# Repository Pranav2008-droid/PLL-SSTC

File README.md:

# PLL SSTC

## Overview
The PLL SSTC stands for Phase Locked Loop Solid State Tesla coil. This device produces high voltage sparks that resemble lightning by exciting a secondary coil at its resonant frequency.

This system tracks the resonant frequency using a Phase Locked Loop (PLL) IC: CD4046. It uses the output from the PLL to drive a full bridge switching circuit at around 300-325VDC.

It also has the capability to play audio through both Amplitude Modulation (AM) and Frequency Modulation (FM). It operates at 250kHz and should switch power in the Kilowatt range.

> ⚠️ High Voltage Warning  
> This project involves potentially lethal voltages and high-frequency/high-power switching. Do not build or operate it unless you understand the relevant electrical safety risks.

## Gate Driver
I'm using a TC4428 paired with 2 N-channel/P-channel dual MOSFET ICs to produce an amplified signal capable of producing higher driving currents. Any MOSFET driving IC with one inverting and one non-inverting output should work in the PCB, such as the UCC27425.

## GDT
The Gate Drive Transformer must be large enough to not saturate from driving currents and be of the correct material to work properly under such high frequencies.

## Mosfets
My circuit shows IRFP460s as the full bridge switches, but they are a bit outdated and inefficient. Much better alternatives exist — IGBTs can also be used instead.

## Primary
Make sure the primary impedance is high enough such that your switches can handle the currents.

## Demo
Demo of the amplitude modification music played through an attiny interupter: https://www.youtube.com/shorts/cHrE9xm2R9Q

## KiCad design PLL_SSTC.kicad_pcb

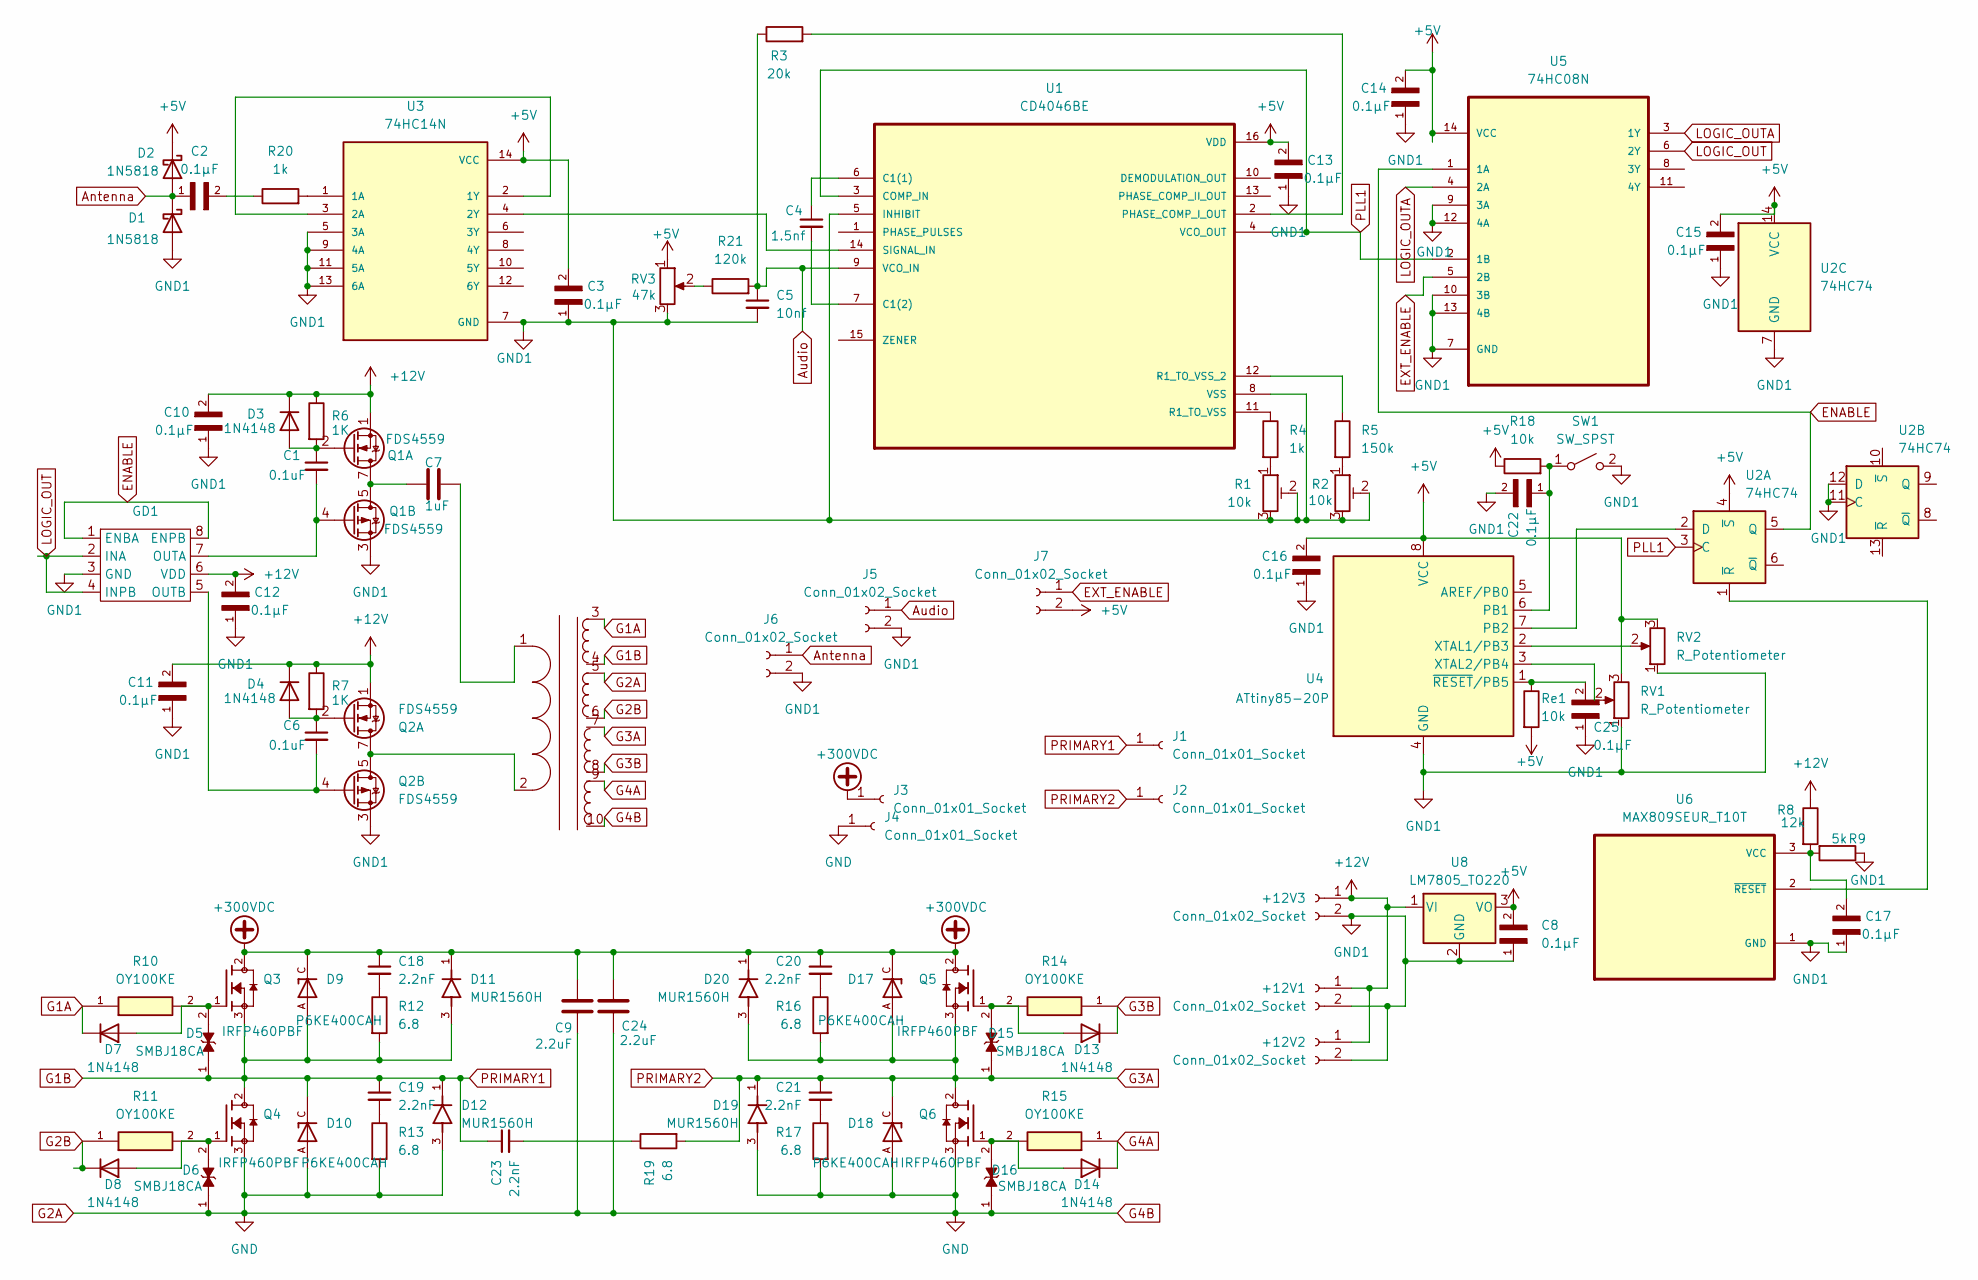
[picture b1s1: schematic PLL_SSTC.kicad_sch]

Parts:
+12V1, +12V2, +12V3: Conn_01x02_Socket; PinHeader_1x02_P2.54mm_Vertical
C1, C6: 0.1uF; C_0603_1608Metric_Pad1.08x0.95mm_HandSolder
C2, C3, C8, C10, C11, C12, C13, C14, C15, C16, C17, C22, C25: 0.1µF; C_0603_1608Metric_Pad1.08x0.95mm_HandSolder; PARTREV 081816
C4: 1.5nf; C_Rect_L7.0mm_W2.5mm_P5.00mm
C5: 10nf; C_Rect_L7.0mm_W2.5mm_P5.00mm
C7: 1uF; C_Rect_L31.5mm_W15.0mm_P27.50mm_MKS4
C9, C24: 2.2uF; C_Rect_L31.5mm_W15.0mm_P27.50mm_MKS4
C18, C19, C20, C21, C23: 2.2nF; C_Rect_L7.0mm_W2.5mm_P5.00mm
D1, D2: 1N5818; D_DO-41_SOD81_P10.16mm_Horizontal
D3, D4, D7, D8, D13, D14: 1N4148; D_DO-35_SOD27_P7.62mm_Horizontal
D5, D6, D15, D16: SMBJ18CA; DIOM4336X265N; PARTREV I2102
D9, D10, D17, D18: P6KE400CAH; DIOAD1300W80L670D310; PARTREV K2105
D11, D12, D19, D20: MUR1560H; TO508P997X444X1905-2; PARTREV F
GD1: DIP-8_W7.62mm_LongPads
J1, J2, J3, J4: Conn_01x01_Socket; SolderWire-4sqmm_1x01_D3mm_OD6mm
J5, J6, J7: Conn_01x02_Socket; TerminalBlock_Phoenix_MKDS-3-2-5.08_1x02_P5.08mm_Horizontal
Q1, Q2: FDS4559; SOIC-8_3.9x4.9mm_P1.27mm
Q3, Q4, Q5, Q6: IRFP460PBF; TO546P1587X531X2511-3; PARTREV A
R1, R2: 10k; TRIM_3296W-1-250
R3: 20k; R_Axial_DIN0207_L6.3mm_D2.5mm_P10.16mm_Horizontal
R4, R20: 1k; R_Axial_DIN0207_L6.3mm_D2.5mm_P10.16mm_Horizontal
R5: 150k; R_Axial_DIN0207_L6.3mm_D2.5mm_P10.16mm_Horizontal
R6, R7: 1K; R_Axial_DIN0207_L6.3mm_D2.5mm_P10.16mm_Horizontal
R8: 12k; R_Axial_DIN0207_L6.3mm_D2.5mm_P10.16mm_Horizontal
R9: 5k; R_Axial_DIN0207_L6.3mm_D2.5mm_P10.16mm_Horizontal
R10, R11, R14, R15: OY100KE; R_Axial_DIN0414_L11.9mm_D4.5mm_P7.62mm_Vertical; MOUSER_PART_NUMBER 588-OY-10-E
R12, R13, R16, R17, R19: 6.8; R_Axial_DIN0922_L20.0mm_D9.0mm_P7.62mm_Vertical
R18: 10k; R_Axial_DIN0207_L6.3mm_D2.5mm_P10.16mm_Horizontal
R21: 120k; R_Axial_DIN0207_L6.3mm_D2.5mm_P10.16mm_Horizontal
RV1, RV2: R_Potentiometer; Potentiometer_Bourns_3296X_Horizontal
RV3: 47k; Potentiometer_Bourns_3296X_Horizontal
Re1: 10k; R_Axial_DIN0204_L3.6mm_D1.6mm_P1.90mm_Vertical
SW1: SW_SPST; TerminalBlock_4Ucon_1x02_P3.50mm_Horizontal
U1: CD4046BE; DIP794W45P254L1969H508Q16
U2: 74HC74; CERDIP-14_W7.62mm_SideBrazed_LongPads_Socket
U3: 74HC14N; DIP764W47P254L1920H431Q14
U4: ATtiny85-20P; DIP-8_W7.62mm
U5: 74HC08N; DIP254P762X420-14; MPN 74HC08N
U6: MAX809SEUR_T10T; SOT95P237X112-3N
U7: GDT_1P4S
U8: LM7805_TO220; TO-220-3_Vertical

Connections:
+5V: C3.2, C8.2, C13.2, C14.2, C15.2, C16.2, D2.1 (K), J7.2, R18.1, RV1.3, RV2.3, RV3.1, Re1.2, U1.16 (VDD), U2.4 (~S), U2.14 (VCC), U3.14 (VCC), U4.8 (VCC), U5.14 (VCC), U8.3 (VO)
+12V: +12V1.1, +12V2.1, +12V3.1, C10.2, C11.2, C12.2, D3.1 (K), D4.1 (K), GD1.6 (VDD), Q1.1 (S1), Q2.1 (S1), R6.1, R7.1, R8.1, U8.1 (VI)
+300VDC: C9.1, C18.1, C20.1, C24.1, D9.C, D11.1, D17.C, D20.1, J3.1 (Pin_1_1), Q3.2, Q5.2
Antenna: C2.1, D1.1 (K), D2.2 (A), J6.1
Audio: C5.1, J5.1, R3.1, R21.2, U1.9 (VCO_IN)
ENABLE: GD1.1 (ENBA), GD1.8 (ENPB), U2.5 (Q), U5.1 (1A)
EXT_ENABLE: J7.1, U5.5 (2B)
G1A: D7.1 (K), R10.1, U7.3 (1A)
G1B: C19.1, C23.1, D5.1, D9.A, D10.C, D11.3, D12.1, J1.1 (Pin_1_1), Q3.3, Q4.2, R12.2, U7.4 (1B)
G2A: C9.2, C24.2, D6.1, D10.A, D12.3, D16.1, D18.A, D19.3, J4.1 (Pin_1_1), Q4.3, Q6.3, R13.2, R17.2, U7.5 (2A), U7.10 (4B)
G2B: D8.1 (K), R11.1, U7.6 (2B)
G3A: C21.1, D15.1, D17.A, D18.C, D19.1, D20.3, J2.1 (Pin_1_1), Q5.3, Q6.2, R16.2, R19.2, U7.7 (3A)
G3B: D13.1 (K), R14.1, U7.8 (3B)
G4A: D14.1 (K), R15.1, U7.9 (4A)
GND1: +12V1.2, +12V2.2, +12V3.2, C3.1, C5.2, C8.1, C10.1, C11.1, C12.1, C13.1, C14.1, C15.1, C16.1, C17.1, C22.2, C25.1, D1.2 (A), GD1.3 (GND), J5.2, J6.2, Q1.3 (S2), Q2.3 (S2), R1.2, R1.3, R2.2, R2.3, R9.1, RV1.1, RV2.1, RV3.3, SW1.2 (B), U1.5 (INHIBIT), U1.8 (VSS), U2.7 (GND), U2.11 (C), U2.12 (D), U3.5 (3A), U3.7 (GND), U3.9 (4A), U3.11 (5A), U3.13 (6A), U4.4 (GND), U5.7 (GND), U5.9 (3A), U5.10 (3B), U5.12 (4A), U5.13 (4B), U6.1 (GND), U8.2 (GND)
LOGIC_OUT: GD1.2 (INA), GD1.4 (INPB), U5.6 (2Y)
LOGIC_OUTA: U5.3 (1Y), U5.4 (2A)
unnamed: C2.2, R20.1
unnamed: C7.1, Q1.5 (D2), Q1.6 (D2), Q1.7 (D1), Q1.8 (D1)
unnamed: C18.2, R12.1
unnamed: C19.2, R13.1
unnamed: C20.2, R16.1
unnamed: C21.2, R17.1
unnamed: C23.2, R19.1
unnamed: C1.1, D3.2 (A), Q1.2 (G1), R6.2
unnamed: C6.1, D4.2 (A), Q2.2 (G1), R7.2
unnamed: D5.2, D7.2 (A), Q3.1, R10.2
unnamed: D6.2, D8.2 (A), Q4.1, R11.2
unnamed: D13.2 (A), D15.2, Q5.1, R14.2
unnamed: D14.2 (A), D16.2, Q6.1, R15.2
unnamed: C1.2, GD1.7 (OUTA), Q1.4 (G2)
unnamed: C6.2, GD1.5 (OUTB), Q2.4 (G2)
unnamed: R1.1, R4.2
unnamed: R2.1, R5.2
unnamed: R21.1, RV3.2
unnamed: C22.1, R18.2, SW1.1 (A), U4.6 (PB1)
unnamed: C4.1, U1.6 (C1(1))
unnamed: C4.2, U1.7 (C1(2))
unnamed: R3.2, U1.2 (PHASE_COMP_I_OUT)
unnamed: R4.1, U1.11 (R1_TO_VSS)
unnamed: R5.1, U1.12 (R1_TO_VSS_2)
unnamed: U1.14 (SIGNAL_IN), U3.4 (2Y)
unnamed: U2.2 (D), U4.7 (PB2)
unnamed: U2.1 (~R), U6.2 (~RESET)
unnamed: R20.2, U3.1 (1A)
unnamed: U3.2 (1Y), U3.3 (2A)
unnamed: RV2.2, U4.2 (XTAL1/PB3)
unnamed: RV1.2, U4.3 (XTAL2/PB4)
unnamed: C25.2, Re1.1, U4.1 (~RESET/PB5)
unnamed: C17.2, R8.2, R9.2, U6.3 (VCC)
unnamed: C7.2, U7.1 (PA)
unnamed: Q2.5 (D2), Q2.6 (D2), Q2.7 (D1), Q2.8 (D1), U7.2 (PB)
PLL1: U1.3 (COMP_IN), U1.4 (VCO_OUT), U2.3 (C), U5.2 (1B)

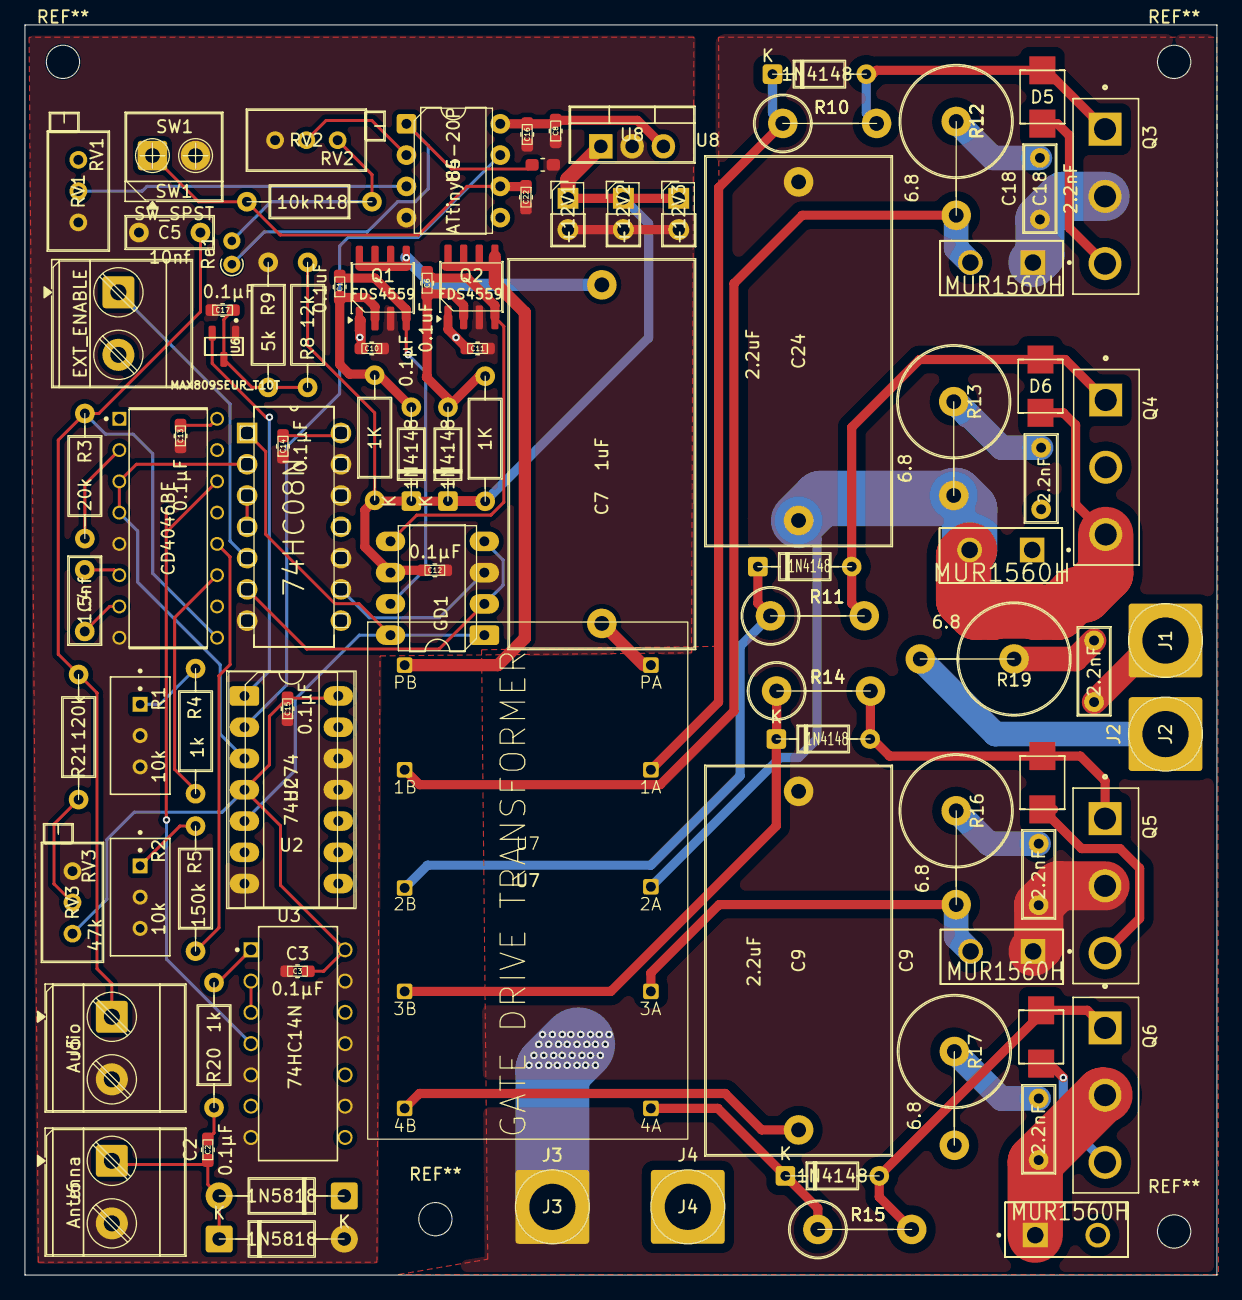
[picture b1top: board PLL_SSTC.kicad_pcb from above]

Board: 2 copper layers, 96.8 x 101.5 mm, 92 parts (0 on the bottom side), 53 nets.
